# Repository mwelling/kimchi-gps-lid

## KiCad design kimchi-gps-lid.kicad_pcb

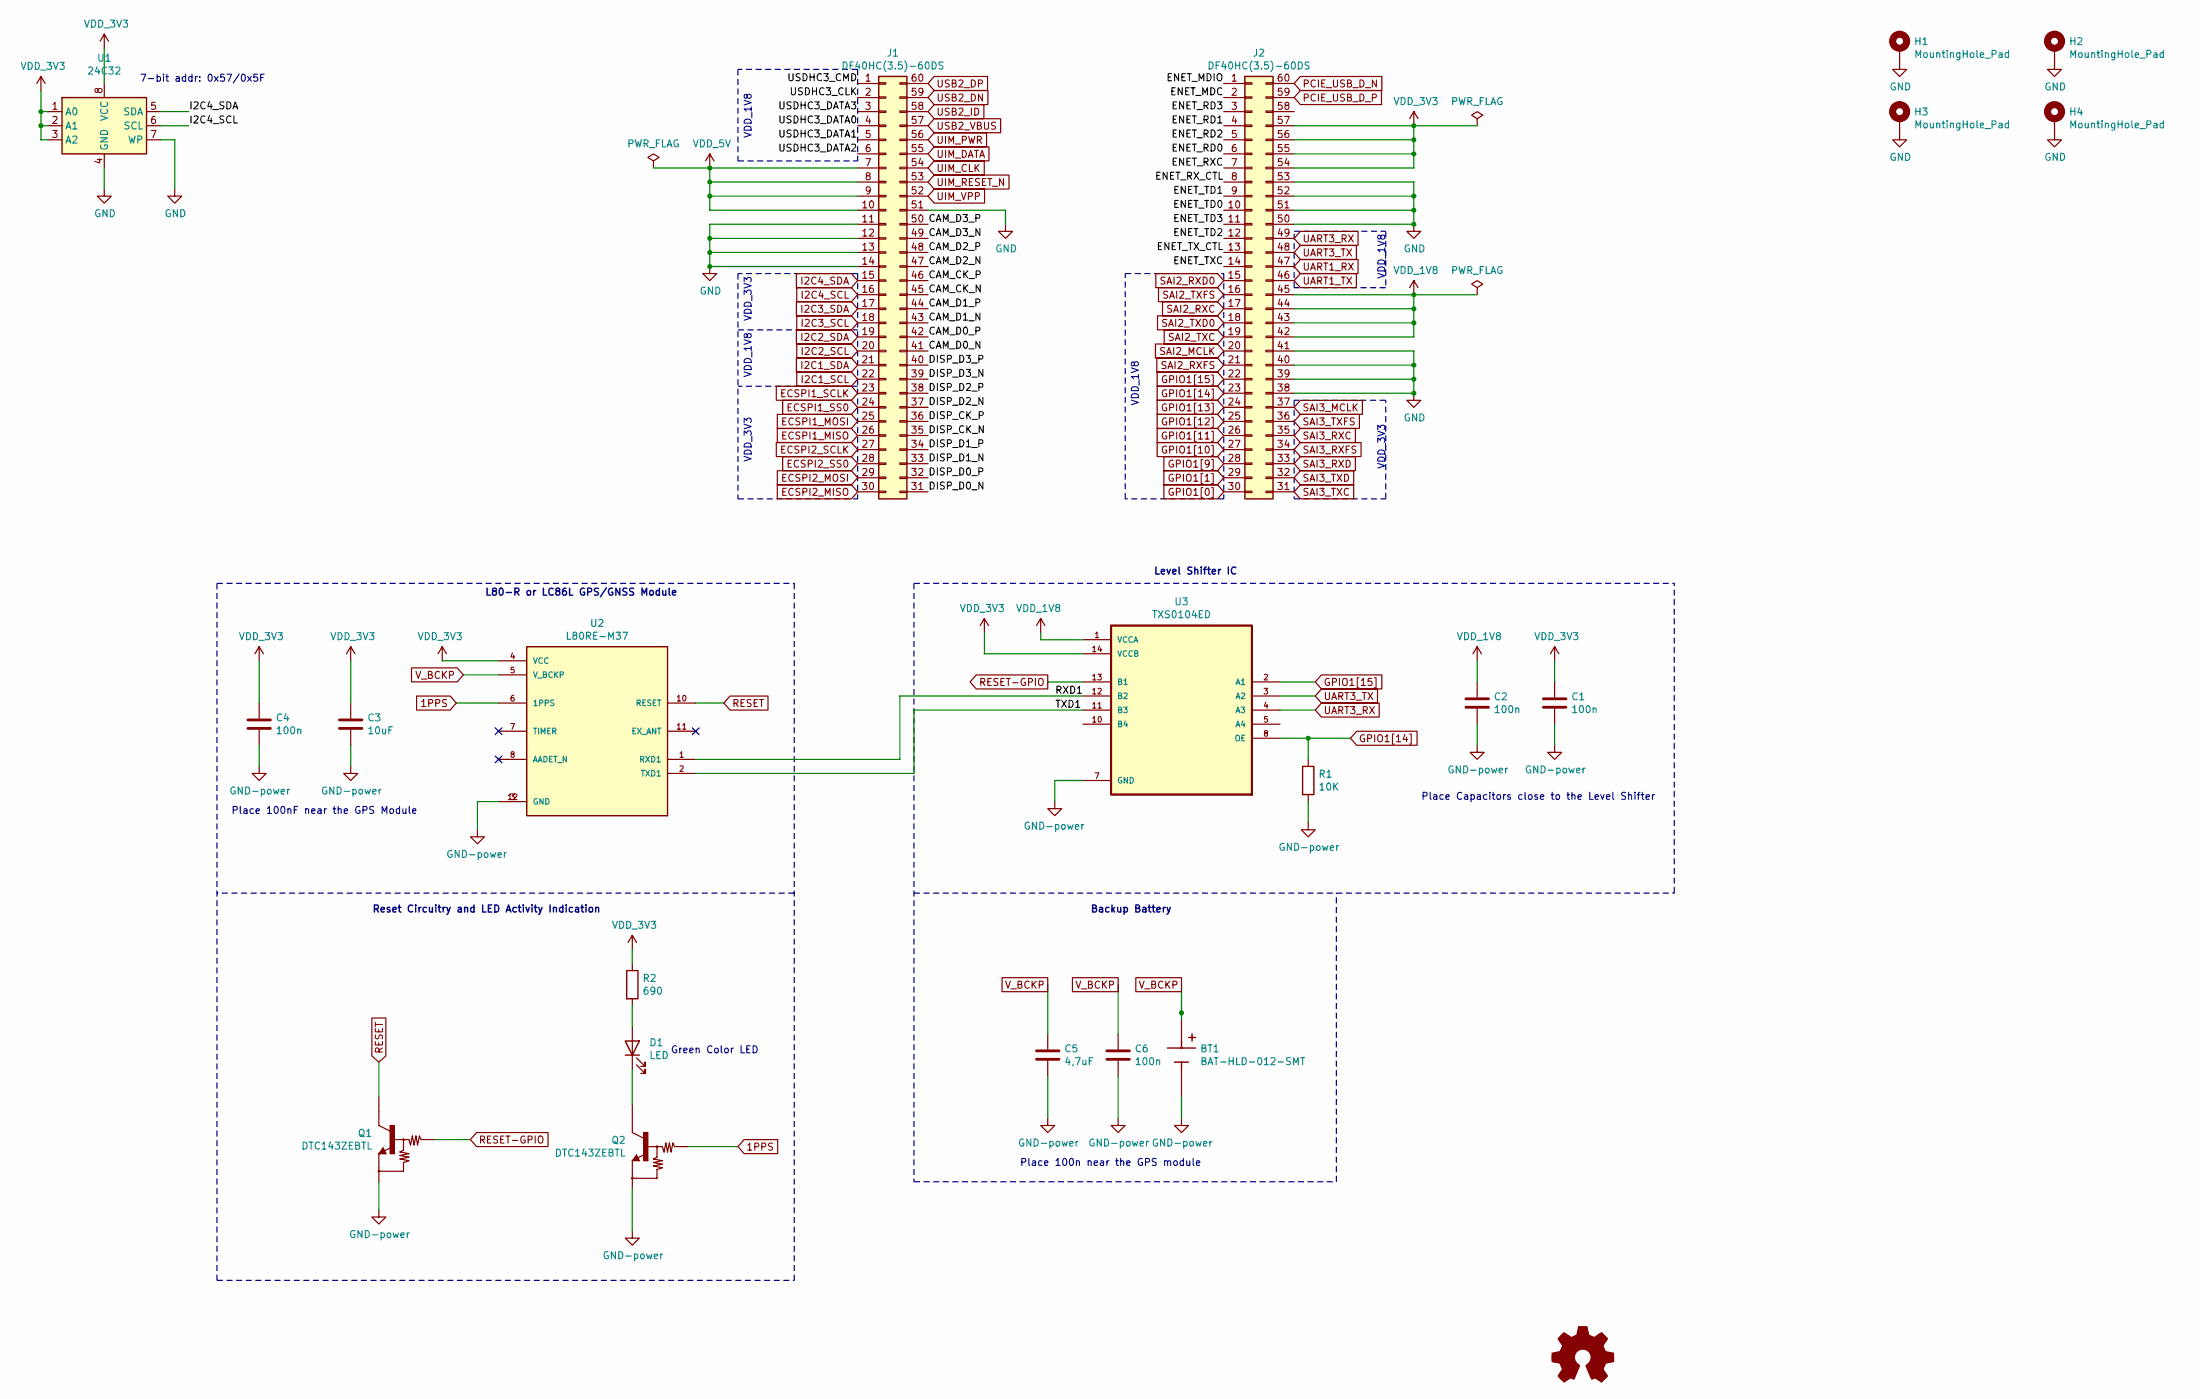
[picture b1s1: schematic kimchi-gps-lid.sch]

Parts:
BT1: BAT-HLD-012-SMT; BAT_BAT-HLD-012-SMT; PARTREV A
C1, C2, C4, C6: 100n; C_0603_1608Metric
C3: 10uF; C_0603_1608Metric
C5: 4,7uF; C_0603_1608Metric
D1: LED; LED_0603_1608Metric
H1, H2, H3, H4: MountingHole_Pad; MountingHole_3mm_Pad
J1, J2: DF40HC(3.5)-60DS
LOGO1: Logo_Open_Hardware_Small; OSHW-Logo_5.7x6mm_SilkScreen
Q1, Q2: DTC143ZEBTL; SOTFL50P160X85-3N; PARTREV 004
R1: 10K; R_0603_1608Metric
R2: 690; R_0603_1608Metric
U1: 24C32; DFN-8-1EP_3x2mm_P0.5mm_EP1.36x1.46mm; Part M24C32-FMC6TG
U2: L80RE-M37; XCVR_L80RE-M37
U3: TXS0104ED; SOIC127P600X175-14N

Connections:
1PPS: Q2.1, U2.6 (1PPS)
/CAM_CK_N: J1.45
/CAM_CK_P: J1.46
/CAM_D0_N: J1.41
/CAM_D0_P: J1.42
/CAM_D1_N: J1.43
/CAM_D1_P: J1.44
/CAM_D2_N: J1.47
/CAM_D2_P: J1.48
/CAM_D3_N: J1.49
/CAM_D3_P: J1.50
/DISP_CK_N: J1.35
/DISP_CK_P: J1.36
/DISP_D0_N: J1.31
/DISP_D0_P: J1.32
/DISP_D1_N: J1.33
/DISP_D1_P: J1.34
/DISP_D2_N: J1.37
/DISP_D2_P: J1.38
/DISP_D3_N: J1.39
/DISP_D3_P: J1.40
/ENET_MDC: J2.2
/ENET_MDIO: J2.1
/ENET_RD0: J2.6
/ENET_RD1: J2.4
/ENET_RD2: J2.5
/ENET_RD3: J2.3
/ENET_RXC: J2.7
/ENET_RX_CTL: J2.8
/ENET_TD0: J2.10
/ENET_TD1: J2.9
/ENET_TD2: J2.12
/ENET_TD3: J2.11
/ENET_TXC: J2.14
/ENET_TX_CTL: J2.13
/RXD1: U2.1 (RXD1), U3.12 (B2)
/TXD1: U2.2 (TXD1), U3.11 (B3)
/USDHC3_CLK: J1.2
/USDHC3_CMD: J1.1
/USDHC3_DATA0: J1.4
/USDHC3_DATA1: J1.5
/USDHC3_DATA2: J1.6
/USDHC3_DATA3: J1.3
ECSPI1_MISO: J1.26
ECSPI1_MOSI: J1.25
ECSPI1_SCLK: J1.23
ECSPI1_SS0: J1.24
ECSPI2_MISO: J1.30
ECSPI2_MOSI: J1.29
ECSPI2_SCLK: J1.27
ECSPI2_SS0: J1.28
GPIO1[0]: J2.30
GPIO1[1]: J2.29
GPIO1[9]: J2.28
GPIO1[10]: J2.27
GPIO1[11]: J2.26
GPIO1[12]: J2.25
GPIO1[13]: J2.24
GPIO1[14]: J2.23, R1.1, U3.8 (OE)
GPIO1[15]: J2.22, U3.2 (A1)
I2C1_SCL: J1.22
I2C1_SDA: J1.21
I2C2_SCL: J1.20
I2C2_SDA: J1.19
I2C3_SCL: J1.18
I2C3_SDA: J1.17
I2C4_SCL: J1.16, U1.6 (SCL)
I2C4_SDA: J1.15, U1.5 (SDA)
unnamed: D1.1 (K), Q2.3
unnamed: D1.2 (A), R2.2
PCIE_USB_D_N: J2.60
PCIE_USB_D_P: J2.59
RESET: Q1.3, U2.10 (RESET)
RESET-GPIO: Q1.1, U3.13 (B1)
SAI2_MCLK: J2.20
SAI2_RXC: J2.17
SAI2_RXD0: J2.15
SAI2_RXFS: J2.21
SAI2_TXC: J2.19
SAI2_TXD0: J2.18
SAI2_TXFS: J2.16
SAI3_MCLK: J2.37
SAI3_RXC: J2.35
SAI3_RXD: J2.33
SAI3_RXFS: J2.34
SAI3_TXC: J2.31
SAI3_TXD: J2.32
SAI3_TXFS: J2.36
UART1_RX: J2.47
UART1_TX: J2.46
UART3_RX: J2.49, U3.4 (A3)
UART3_TX: J2.48, U3.3 (A2)
UIM_CLK: J1.54
UIM_DATA: J1.55
UIM_PWR: J1.56
UIM_RESET_N: J1.53
UIM_VPP: J1.52
USB2_DN: J1.59
USB2_DP: J1.60
USB2_ID: J1.58
USB2_VBUS: J1.57
VDD_1V8: C2.1, J2.42, J2.43, J2.44, J2.45, U3.1 (VCCA)
VDD_3V3: C1.1, C3.1, C4.1, J2.54, J2.55, J2.56, J2.57, R2.1, U1.1 (A0), U1.2 (A1), U1.3 (A2), U1.8 (VCC), U2.4 (VCC), U3.14 (VCCB)
VDD_5V: J1.7, J1.8, J1.9, J1.10
V_BCKP: BT1.P1, BT1.P2, C5.1, C6.1, U2.5 (V_BCKP)

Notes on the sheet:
7-bit addr: 0x57/0x5F
VDD_1V8
VDD_3V3
L80-R or LC86L GPS/GNSS Module
Level Shifter IC
Place 100nF near the GPS Module
Reset Circuitry and LED Activity Indication
Green Color LED
Place Capacitors close to the Level Shifter
Backup Battery
Place 100n near the GPS module

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
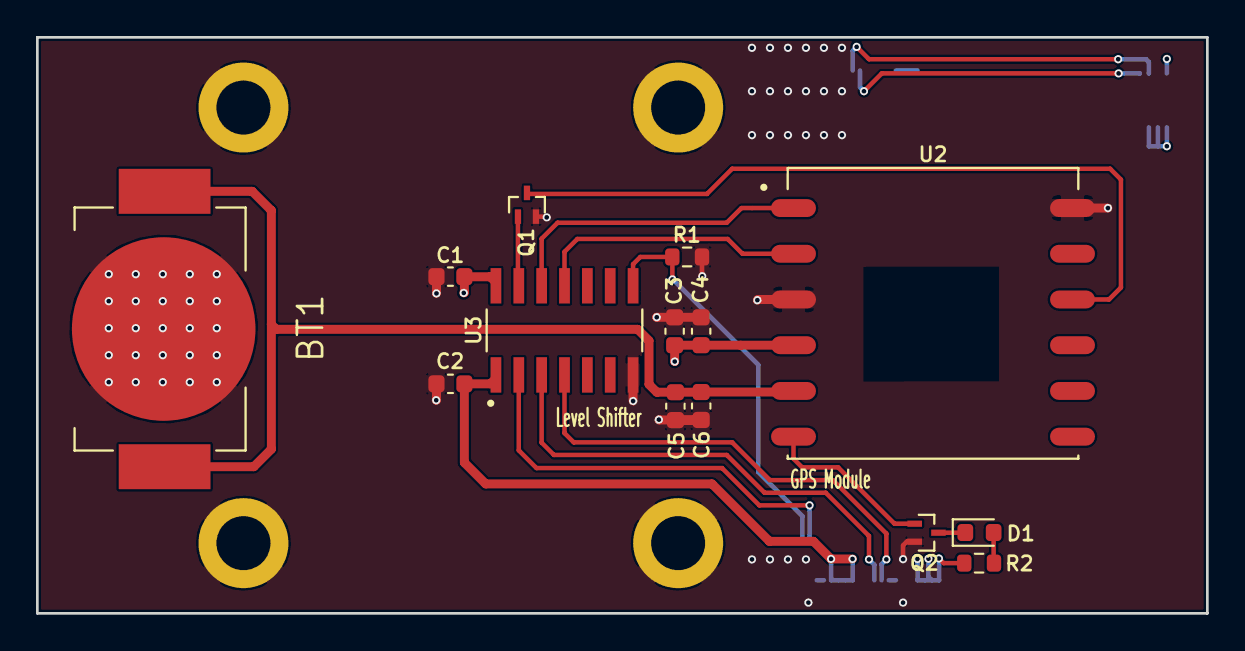
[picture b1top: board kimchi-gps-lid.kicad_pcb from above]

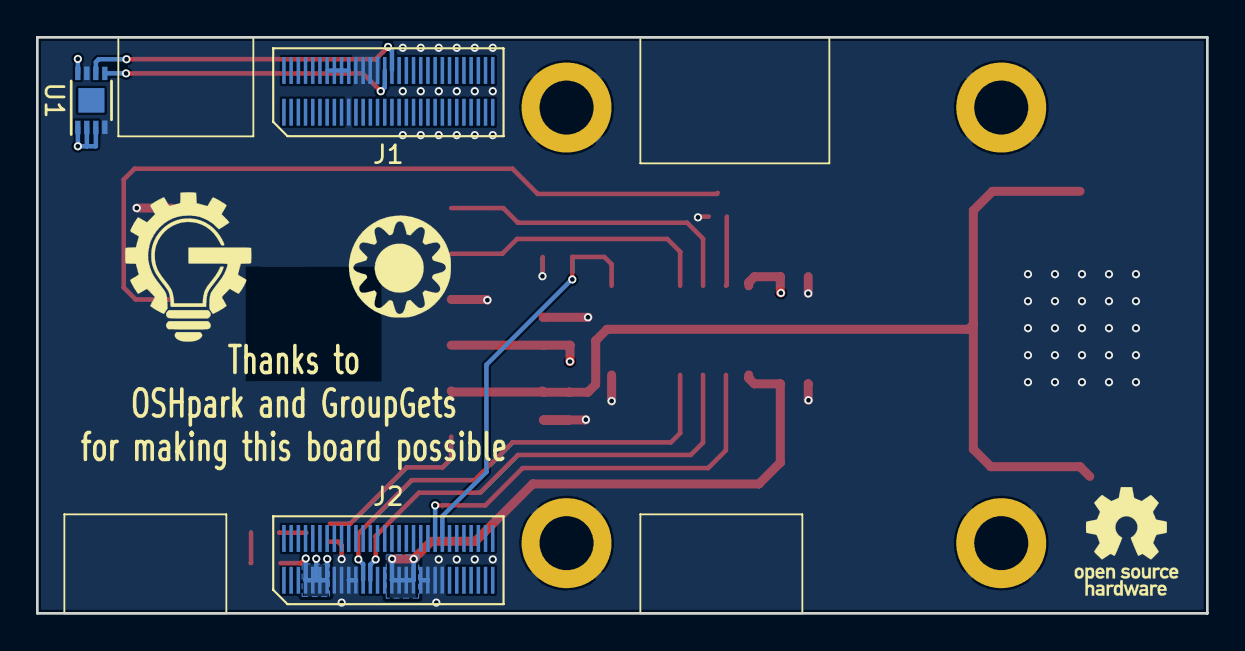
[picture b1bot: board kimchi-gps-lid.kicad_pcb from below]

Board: 4 copper layers, 65.0 x 32.0 mm, 22 parts (4 on the bottom side), 18 nets.

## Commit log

2020-12-16 Instantiate kicad template for gps lid
2021-01-01 Creating Schematic for the GPS LID
    Addition of schematic, datasheets,footprints and 3D Files.
    Signed of by: Thore Krug opensource[at]thorekrug.de
2021-01-01 Fix Capacitor Value
2021-01-06 Completed routing, minor fixes remaining
2021-01-06 Updated routing to reduce vias and cross-overs
2021-01-06 Minor change in VDD_1v8 routing
2021-01-07 Fixed silkscreen and added square keepout under gps module
2021-01-10 Update layout and routing
2021-01-19 Added oshpark and group gets logo to silkscreen
2021-01-25 Changed value of LED resistor according to requirements of green LED
